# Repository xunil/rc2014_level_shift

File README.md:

# Voltage level translator card for RC2014
This is a design for an add-on card for the [RC2014 Z80 Retro computer kit](https://rc2014.co.uk/) which provides a bidirectional, voltage level translated bus interface.  The pinout of the IDC connector is designed for direct connection to a Terasic DE0 Nano FPGA development board, which features an Altera Cyclone IV FPGA.  A separate 0.1" pin header row is included in the design for use with other peripherals.

This design is for the original RC2014 backplane, not the Backplane Pro.

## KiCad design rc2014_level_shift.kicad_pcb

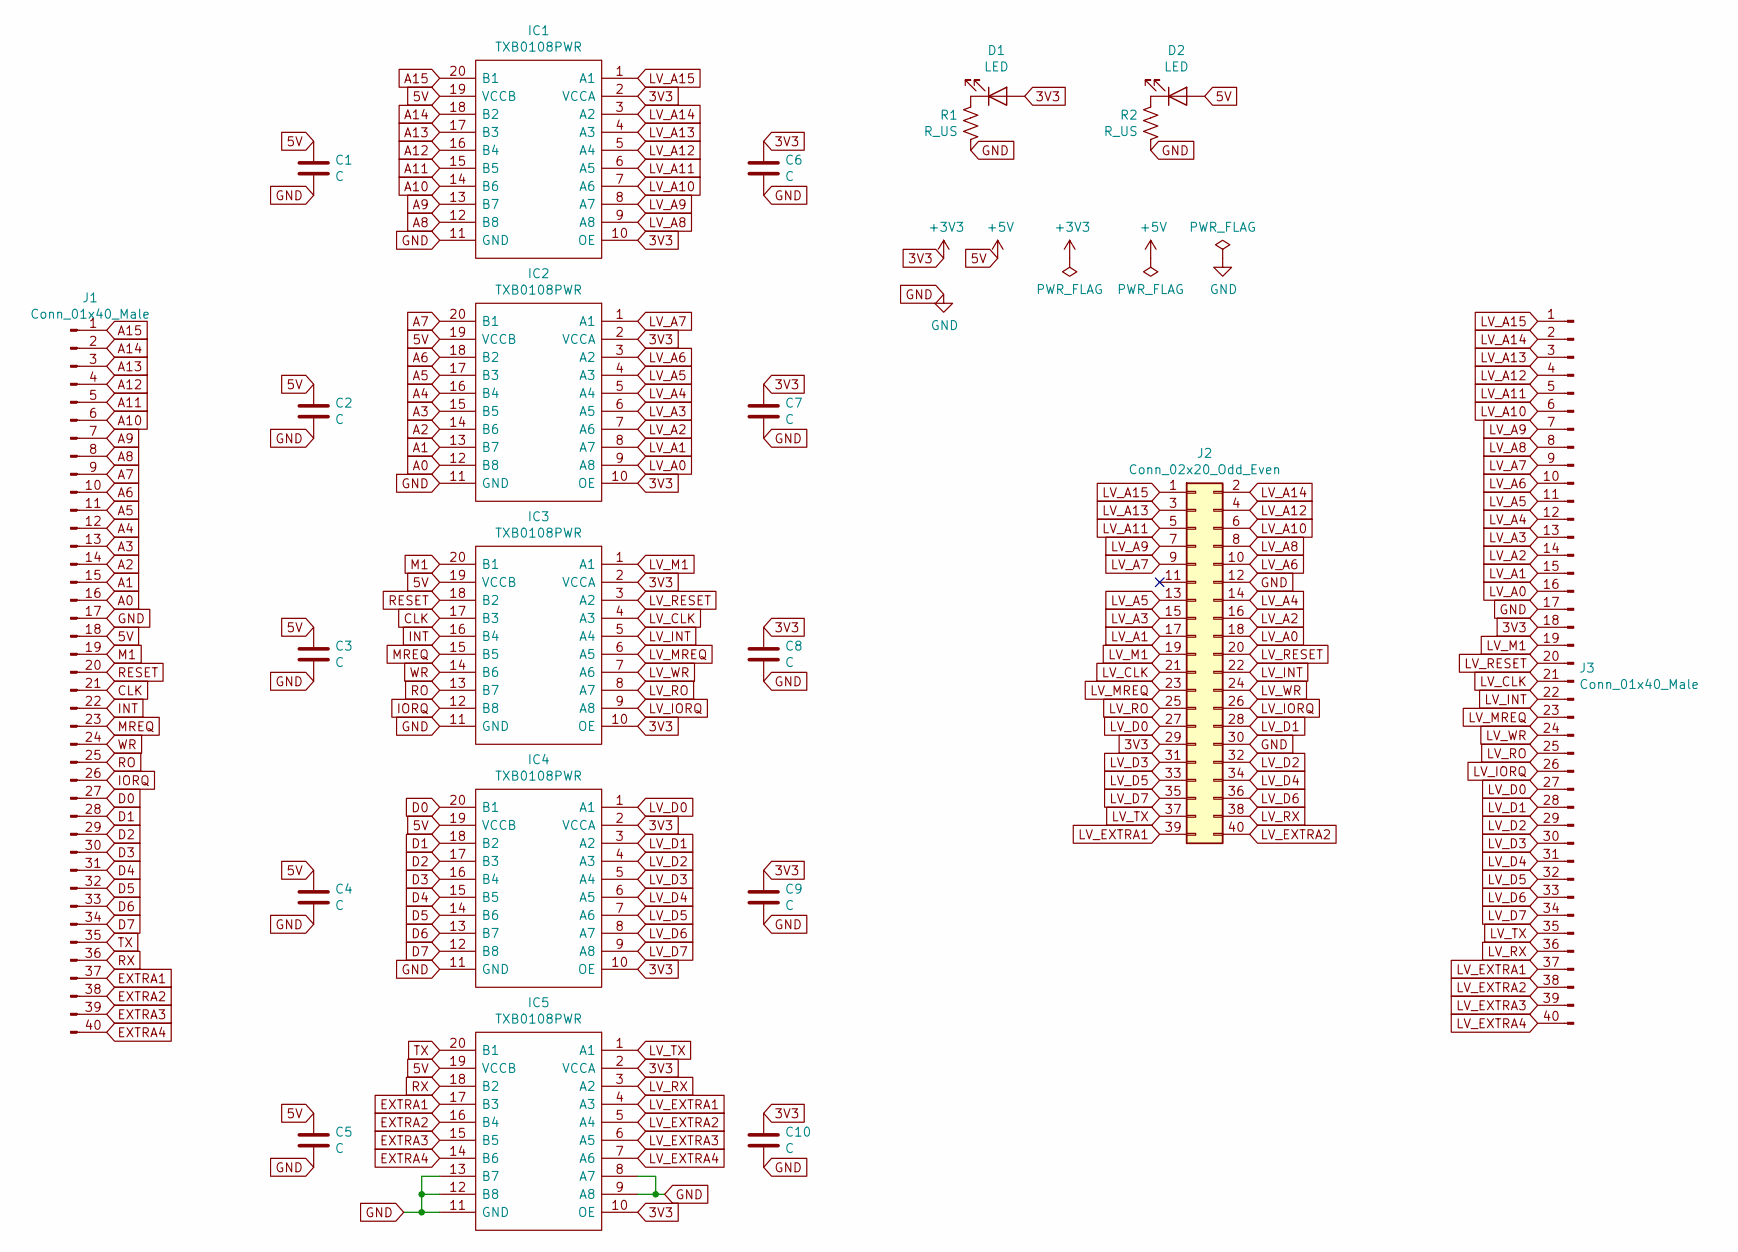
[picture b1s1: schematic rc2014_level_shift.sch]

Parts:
C1, C2, C3, C4, C5, C6, C7, C8, C9, C10: C; C_0603_1608Metric_Pad1.05x0.95mm_HandSolder
D1, D2: LED; LED_D3.0mm
IC1, IC2, IC3, IC4, IC5: TXB0108PWR; TSSOP-20_4.4x6.5mm_P0.65mm; Mouser Part Number 595-TXB0108PWR
J1, J3: Conn_01x40_Male; PinHeader_1x40_P2.54mm_Vertical
J2: Conn_02x20_Odd_Even; IDC-Header_2x20_P2.54mm_Horizontal
R1, R2: R_US; R_0603_1608Metric_Pad1.05x0.95mm_HandSolder

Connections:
3V3: C6.1, C7.1, C8.1, C9.1, C10.1, D1.2 (A), IC1.2 (VCCA), IC1.10 (OE), IC2.2 (VCCA), IC2.10 (OE), IC3.2 (VCCA), IC3.10 (OE), IC4.2 (VCCA), IC4.10 (OE), IC5.2 (VCCA), IC5.10 (OE), J2.29, J3.18
5V: C1.1, C2.1, C3.1, C4.1, C5.1, D2.2 (A), IC1.19 (VCCB), IC2.19 (VCCB), IC3.19 (VCCB), IC4.19 (VCCB), IC5.19 (VCCB), J1.18
A0: IC2.12 (B8), J1.16
A1: IC2.13 (B7), J1.15
A2: IC2.14 (B6), J1.14
A3: IC2.15 (B5), J1.13
A4: IC2.16 (B4), J1.12
A5: IC2.17 (B3), J1.11
A6: IC2.18 (B2), J1.10
A7: IC2.20 (B1), J1.9
A8: IC1.12 (B8), J1.8
A9: IC1.13 (B7), J1.7
A10: IC1.14 (B6), J1.6
A11: IC1.15 (B5), J1.5
A12: IC1.16 (B4), J1.4
A13: IC1.17 (B3), J1.3
A14: IC1.18 (B2), J1.2
A15: IC1.20 (B1), J1.1
CLK: IC3.17 (B3), J1.21
D0: IC4.20 (B1), J1.27
D1: IC4.18 (B2), J1.28
D2: IC4.17 (B3), J1.29
D3: IC4.16 (B4), J1.30
D4: IC4.15 (B5), J1.31
D5: IC4.14 (B6), J1.32
D6: IC4.13 (B7), J1.33
D7: IC4.12 (B8), J1.34
EXTRA1: IC5.17 (B3), J1.37
EXTRA2: IC5.16 (B4), J1.38
EXTRA3: IC5.15 (B5), J1.39
EXTRA4: IC5.14 (B6), J1.40
GND: C1.2, C2.2, C3.2, C4.2, C5.2, C6.2, C7.2, C8.2, C9.2, C10.2, IC1.11 (GND), IC2.11 (GND), IC3.11 (GND), IC4.11 (GND), IC5.8 (A7), IC5.9 (A8), IC5.11 (GND), IC5.12 (B8), IC5.13 (B7), J1.17, J2.12, J2.30, J3.17, R1.2, R2.2
INT: IC3.16 (B4), J1.22
IORQ: IC3.12 (B8), J1.26
LV_A0: IC2.9 (A8), J2.18, J3.16
LV_A1: IC2.8 (A7), J2.17, J3.15
LV_A2: IC2.7 (A6), J2.16, J3.14
LV_A3: IC2.6 (A5), J2.15, J3.13
LV_A4: IC2.5 (A4), J2.14, J3.12
LV_A5: IC2.4 (A3), J2.13, J3.11
LV_A6: IC2.3 (A2), J2.10, J3.10
LV_A7: IC2.1 (A1), J2.9, J3.9
LV_A8: IC1.9 (A8), J2.8, J3.8
LV_A9: IC1.8 (A7), J2.7, J3.7
LV_A10: IC1.7 (A6), J2.6, J3.6
LV_A11: IC1.6 (A5), J2.5, J3.5
LV_A12: IC1.5 (A4), J2.4, J3.4
LV_A13: IC1.4 (A3), J2.3, J3.3
LV_A14: IC1.3 (A2), J2.2, J3.2
LV_A15: IC1.1 (A1), J2.1, J3.1
LV_CLK: IC3.4 (A3), J2.21, J3.21
LV_D0: IC4.1 (A1), J2.27, J3.27
LV_D1: IC4.3 (A2), J2.28, J3.28
LV_D2: IC4.4 (A3), J2.32, J3.29
LV_D3: IC4.5 (A4), J2.31, J3.30
LV_D4: IC4.6 (A5), J2.34, J3.31
LV_D5: IC4.7 (A6), J2.33, J3.32
LV_D6: IC4.8 (A7), J2.36, J3.33
LV_D7: IC4.9 (A8), J2.35, J3.34
LV_EXTRA1: IC5.4 (A3), J2.39, J3.37
LV_EXTRA2: IC5.5 (A4), J2.40, J3.38
LV_EXTRA3: IC5.6 (A5), J3.39
LV_EXTRA4: IC5.7 (A6), J3.40
LV_INT: IC3.5 (A4), J2.22, J3.22
LV_IORQ: IC3.9 (A8), J2.26, J3.26
LV_M1: IC3.1 (A1), J2.19, J3.19
LV_MREQ: IC3.6 (A5), J2.23, J3.23
LV_RESET: IC3.3 (A2), J2.20, J3.20
LV_RO: IC3.8 (A7), J2.25, J3.25
LV_RX: IC5.3 (A2), J2.38, J3.36
LV_TX: IC5.1 (A1), J2.37, J3.35
LV_WR: IC3.7 (A6), J2.24, J3.24
M1: IC3.20 (B1), J1.19
MREQ: IC3.15 (B5), J1.23
unnamed: D1.1 (K), R1.1
unnamed: D2.1 (K), R2.1
RESET: IC3.18 (B2), J1.20
RO: IC3.13 (B7), J1.25
RX: IC5.18 (B2), J1.36
TX: IC5.20 (B1), J1.35
WR: IC3.14 (B6), J1.24

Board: 2 copper layers, 22 parts (0 on the bottom side), 81 nets, no tracks yet.

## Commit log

2020-02-07 Initial import
2020-02-07 Added short README
